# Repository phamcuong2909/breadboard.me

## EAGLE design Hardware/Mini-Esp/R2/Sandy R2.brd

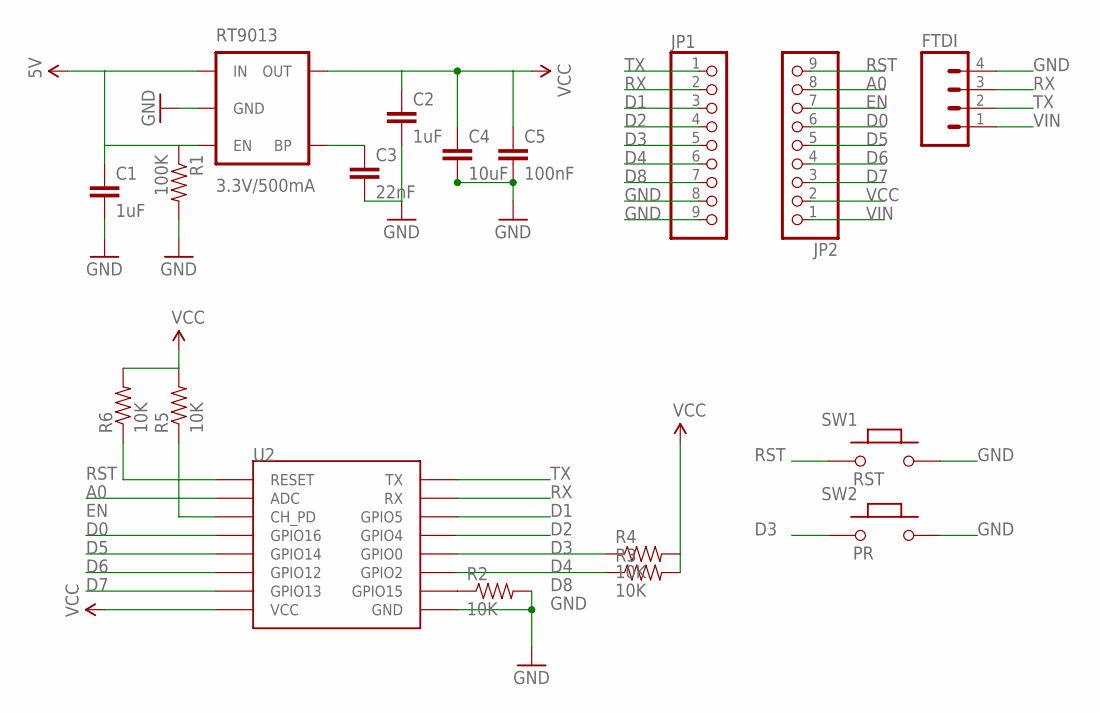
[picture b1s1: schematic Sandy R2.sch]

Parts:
C1, C2: 1uF; 0805
C3: 22nF; 0805
C4: 10uF; 0805
C5: 100nF; 0805
FTDI: M04PTH; 1X04
JP1, JP2: PINHD-1X9; 1X09-BIG
R1: 100K; 0805
R2, R3, R4, R5, R6: 10K; 0805
RT9013: 3.3V/500mA; SOT23-5
SW1: RST; 157SW
SW2: PR; 157SW
U2: ESP12THROUGHOLE; ESP12

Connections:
A0: JP2.8, U2.ADC
BP: C3.1, RT9013.4 (BP)
D0: JP2.6, U2.GPIO16
D1: JP1.3, U2.GPIO5
D2: JP1.4, U2.GPIO4
D3: JP1.5, R4.1, SW2.1, U2.GPIO0
D4: JP1.6, R3.1, U2.GPIO2
D5: JP2.5, U2.GPIO14
D6: JP2.4, U2.GPIO12
D7: JP2.3, U2.GPIO13
D8: JP1.7, R2.1, U2.GPIO15
EN: JP2.7, R5.1, U2.CH_PD
GND: C1.2, C2.2, C3.2, C4.2, C5.2, FTDI.4, JP1.8, JP1.9, R1.2, R2.2, RT9013.2 (GND), SW1.2, SW2.2, U2.GND
RST: JP2.9, R6.1, SW1.1, U2.RESET
RX: FTDI.3, JP1.2, U2.RX
TX: FTDI.2, JP1.1, U2.TX
VCC: C2.1, C4.1, C5.1, JP2.2, R3.2, R4.2, R5.2, R6.2, RT9013.5 (OUT), U2.VCC
VIN: C1.1, FTDI.1, JP2.1, R1.1, RT9013.1 (IN), RT9013.3 (EN)

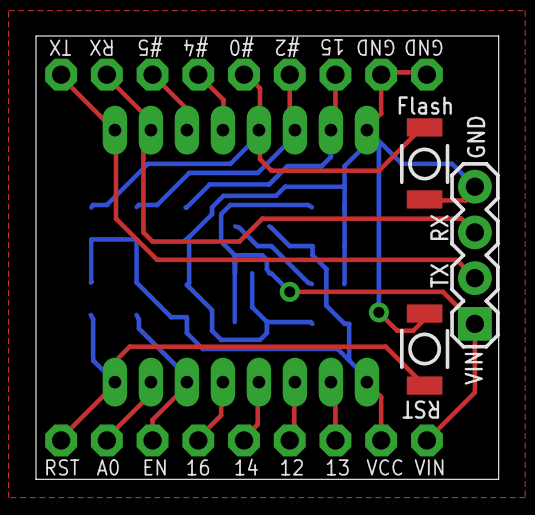
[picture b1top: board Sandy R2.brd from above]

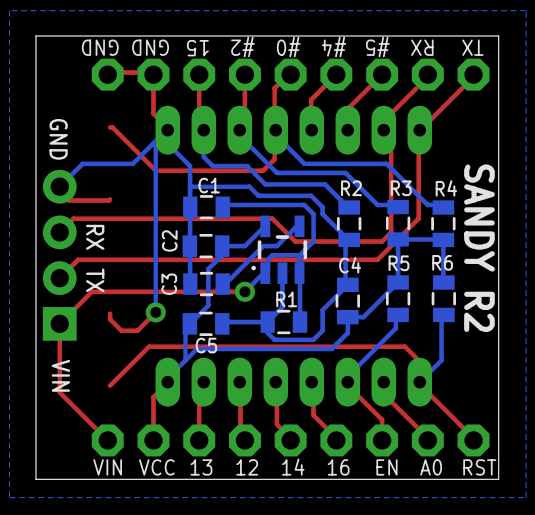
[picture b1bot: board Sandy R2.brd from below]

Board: 2 copper layers, 25.7 x 24.6 mm, 18 parts (12 on the bottom side), 18 nets.

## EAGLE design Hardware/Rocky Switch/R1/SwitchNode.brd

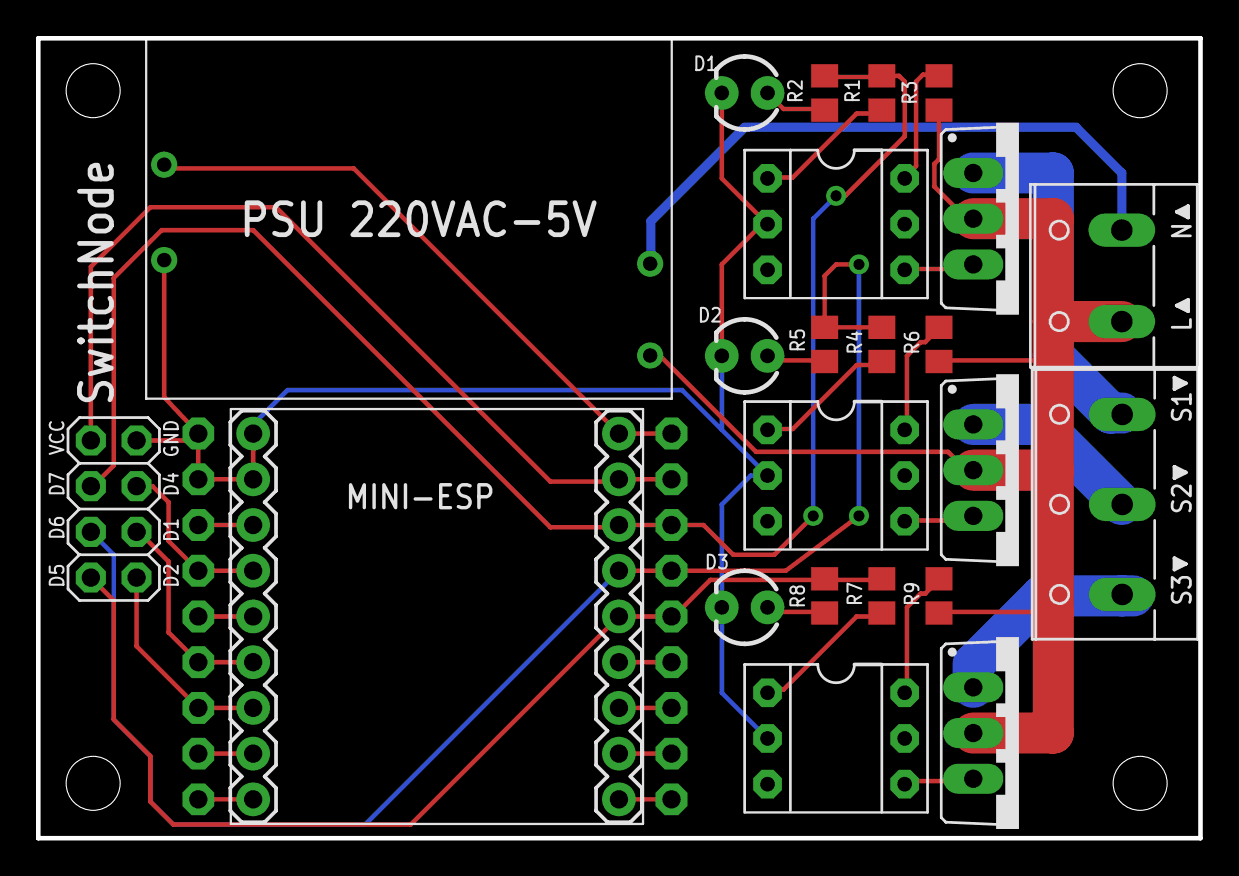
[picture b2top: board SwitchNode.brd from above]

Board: 2 copper layers, 64.6 x 44.4 mm, 35 parts (1 on the bottom side), 34 nets.

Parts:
AC: W237-132
D1, D2, D3: LED3MM
JP1, JP3: 1X09-BIG
JP2: 2X04
OUT: W237-103
R1, R4, R7: 220; R0805
R2, R5, R8: 10K; R0805
R3, R6, R9: 470; R0805
T1, T2, T3: BT138-V; TO220BV
U$1: POWER_SUPPLY_220VAC_5V
U$2: MINI-ESP
U$3, U$4, U$5: MOC3031-M; DIL06
U$6, U$7, U$8, U$9: KFH-M3
U$10: ICON_EXL-S
U$11, U$12, U$13, U$14, U$15: ICON_PIN1_B

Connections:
5V: JP1.1, U$1.5V, U$2.VIN
A0: JP1.8, U$2.A0
AC_L: AC.1, R3.2, R6.2, R9.2, T1.T2, T2.T2, T3.T2, U$1.AC_L
AC_N: AC.2, U$1.AC_N
D0: JP1.6, U$2.D0
D1: JP2.6, JP3.4, U$2.D1
D2: JP2.8, JP3.3, U$2.D2
D3: JP3.5, U$2.D3
D4: JP2.4, JP3.6, U$2.D4
D5: JP1.5, JP2.7, R7.1, R8.1, U$2.D5
D6: JP1.4, JP2.5, R4.1, R5.1, U$2.D6
D7: JP1.3, JP2.3, R1.1, R2.1, U$2.D7
D8: JP3.7, U$2.D8
EN: JP1.7, U$2.EN
GND: D1.K, D2.K, D3.K, JP2.2, JP3.8, JP3.9, U$1.GND, U$2.GND, U$2.GND2, U$3.2, U$4.2, U$5.2
unnamed: R1.2, U$3.1
unnamed: R3.1, U$3.6
unnamed: R4.2, U$4.1
unnamed: D2.A, R5.2
unnamed: R6.1, U$4.6
unnamed: T1.G, U$3.4
unnamed: T2.G, U$4.4
unnamed: R7.2, U$5.1
unnamed: D3.A, R8.2
unnamed: OUT.2, T2.T1
unnamed: R9.1, U$5.6
unnamed: T3.G, U$5.4
unnamed: OUT.1, T3.T1
unnamed: D1.A, R2.2
unnamed: OUT.3, T1.T1
RST: JP1.9, U$2.RST
RX: JP3.2, U$2.RX
TX: JP3.1, U$2.TX
VCC: JP1.2, JP2.1, U$2.VCC

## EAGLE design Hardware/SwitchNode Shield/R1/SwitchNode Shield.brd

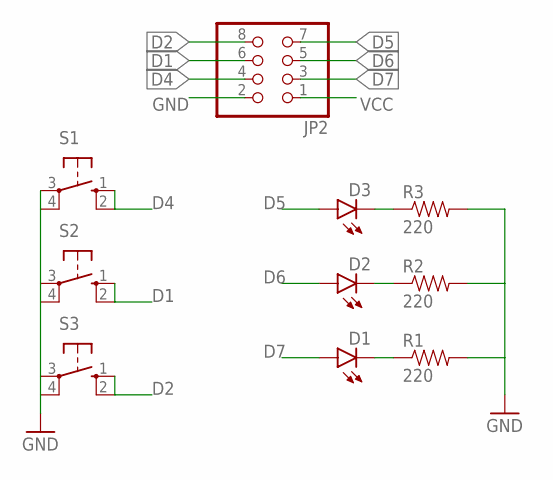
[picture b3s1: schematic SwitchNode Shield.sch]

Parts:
D1, D2, D3: LED3MM
JP2: PINHD-2X4; 2X04
R1, R2, R3: 220; AXIAL-0.3
S1, S2, S3: 40-XX; B3F-40XX

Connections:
D1: JP2.6, S2.1 (S), S2.2 (S1)
D2: JP2.8, S3.1 (S), S3.2 (S1)
D4: JP2.4, S1.1 (S), S1.2 (S1)
D5: D3.A, JP2.7
D6: D2.A, JP2.5
D7: D1.A, JP2.3
GND: JP2.2, R1.P$2 (2), R2.P$2 (2), R3.P$2 (2), S1.3, S1.4 (P1), S2.3, S2.4 (P1), S3.3, S3.4 (P1)
unnamed: D3.K (C), R3.P$1 (1)
unnamed: D2.K (C), R2.P$1 (1)
unnamed: D1.K (C), R1.P$1 (1)
VCC: JP2.1

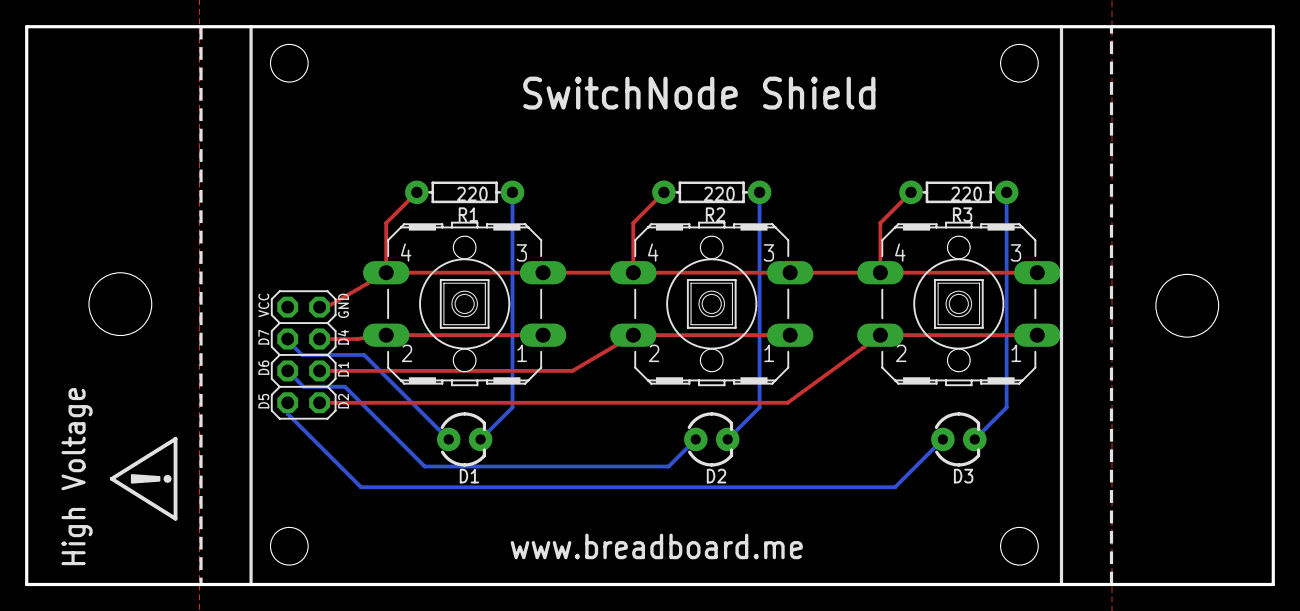
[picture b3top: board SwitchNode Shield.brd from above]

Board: 2 copper layers, 99.3 x 44.4 mm, 17 parts (0 on the bottom side), 10 nets.

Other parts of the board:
U$1, U$2: KFH-M5
U$3: ICON_EXL-S
U$6, U$7, U$8, U$9: KFH-M3

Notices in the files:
parts and their libraries:
SparkFun-Passives: Licensing: Creative Commons ShareAlike 4.0 International - https://creativecommons.org/licenses/by-sa/4.0
SparkFun: Licensing: CC v3.0 Share-Alike You are welcome to use this library for commercial purposes.
penn-engineering: Copyright (C) 2010, Bob Starr
